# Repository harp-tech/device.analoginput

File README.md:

## Harp Analog Input

This device samples simultaneously up to 4 analog signals with 16 bits resolution, low noise and and analog input range of ±10 V for all channels.

### Key Features ###

* 4 ADC channels
* 16bit resolution with an input range of +-10V
* Simultaneous acquisition of all channels
* Threshold detection and event generation

### Connectivity ###

* 4 BNC connectors for analog input
* I/O connector for TTL signals

## Interface ##

The interface with the Harp board can be done through [Bonsai](https://bonsai-rx.org/)

## Licensing ##

Each subdirectory will contain a license or, possibly, a set of licenses if it involves both hardware and software.

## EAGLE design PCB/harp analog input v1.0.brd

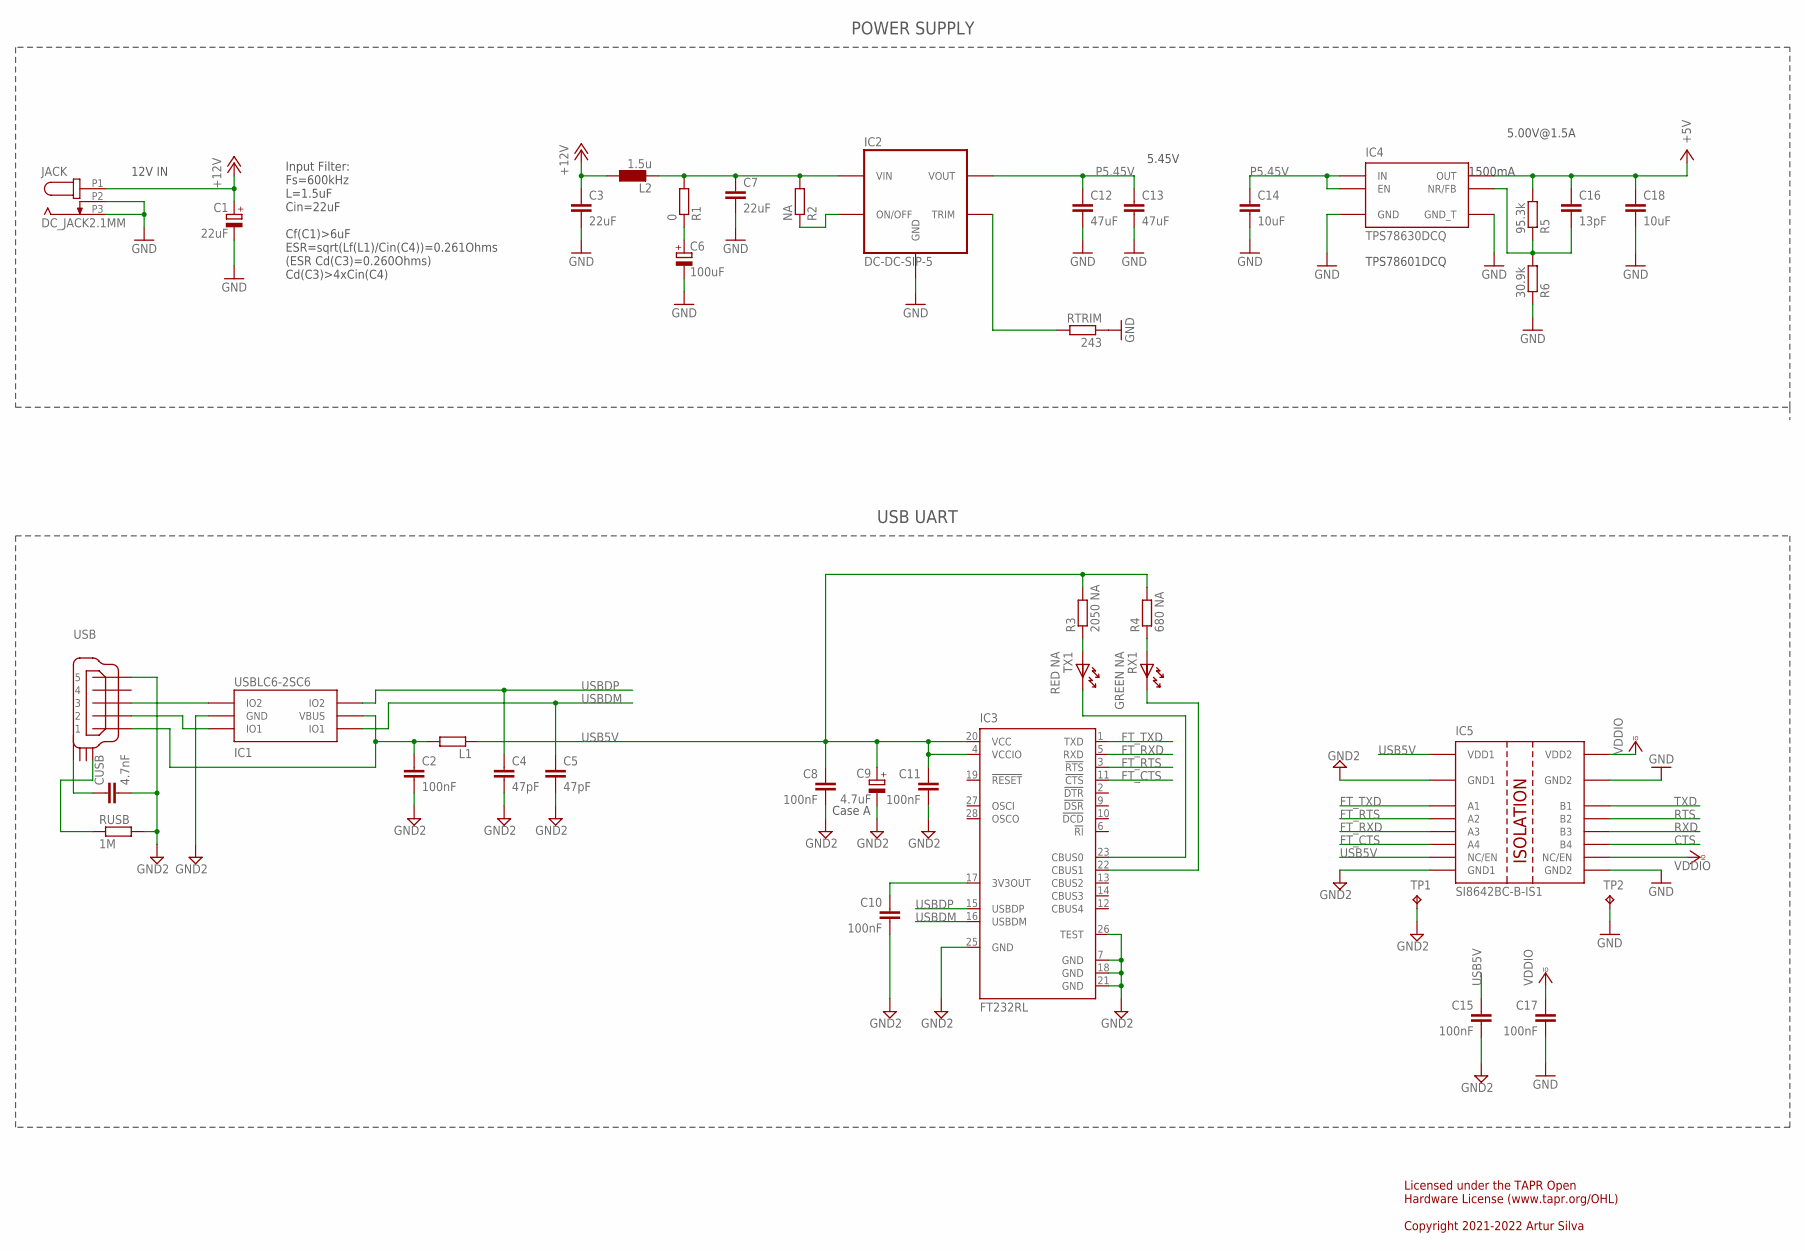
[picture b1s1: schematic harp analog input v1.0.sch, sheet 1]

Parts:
C1: 22uF; CAP_100UF_HAND
C2, C8, C10, C11, C15, C17: 100nF; C0402
C3, C7: 22uF; C1210
C4, C5: 47pF; C0402
C6: 100uF; PANASONIC_E
C9: 4.7uF; A/3216-18W
C12, C13: 47uF; C1210
C14, C18: 10uF; C0603
C16: 13pF; C0402
CUSB: 4.7nF; C0402
IC1: USBLC6-2SC6; SOT23-6L
IC2: DC-DC-SIP-5; SIP-5
IC3: FT232RL; SSOP28
IC4: TPS78630DCQ; SON-8
IC5: SI8642BC-B-IS1; NSOIC-16
JACK: DC_JACK2.1MM; DC_POWER_INPUT_2.1MM
L1: ???; R0805
L2: 1.5u; IND_LPS4012
R1: 0; R0402
R2: NA; R0402
R3: 2050 NA; R0402
R4: 680 NA; R0402
R5: 95.3k; R0402
R6: 30.9k; R0402
RTRIM: 243; R0402
RUSB: 1M; R0402
RX1: GREEN NA; LED_HAND
TP1, TP2: TPTP08SQ; TP08SQ
TX1: RED NA; LED_HAND
USB: USB_MINI_B; 240-0002-1

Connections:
3V3OUT: C10.1, IC3.17 (3V3OUT)
+5V: C16.1, C18.1, IC4.P3 (OUT), IC4.P4 (OUT), R5.2; also elsewhere on the board
+12V: C1.+, C3.1, JACK.P1 (1), L2.1
CTS: IC5.11 (B4); also elsewhere on the board
DCIN: C7.1, IC2.P2 (VIN), L2.2, R1.2, R2.2
FT_CTS: IC3.11 (!CTS), IC5.6 (A4)
FT_RTS: IC3.3 (!RTS), IC5.4 (A2)
FT_RXD: IC3.5 (RXD), IC5.5 (A3)
FT_TXD: IC3.1 (TXD), IC5.3 (A1)
GND: C1.-, C3.2, C6.-, C7.2, C12.2, C13.2, C14.2, C17.2, C18.2, IC2.P3 (GND), IC4.P6 (GND), IC4.P9 (GND_T), IC5.9 (GND2), IC5.15 (GND2), JACK.P2 (2), JACK.P3 (3), R6.1, RTRIM.1, TP2.TP; also elsewhere on the board
GND2: C2.2, C4.2, C5.2, C8.2, C9.-, C10.2, C11.2, C15.2, CUSB.2, IC1.P$2 (GND), IC3.7 (GND), IC3.18 (GND), IC3.21 (GND), IC3.25 (GND), IC3.26 (TEST), IC5.2 (GND1), IC5.8 (GND1), RUSB.2, TP1.TP, USB.P$5 (5)
unnamed: R4.1, RX1.A
unnamed: IC3.22 (CBUS1), RX1.K
unnamed: IC2.P5 (TRIM), RTRIM.2
unnamed: IC1.P$3 (IO2), USB.P$3 (3)
unnamed: CUSB.1, USB.SHIELD_4
unnamed: IC2.P1 (ON/OFF), R2.1
unnamed: C16.2, IC4.P5 (NR/FB), R5.1, R6.2
unnamed: C6.+, R1.1
unnamed: C2.1, IC1.P$5 (VBUS), L1.2, USB.P$1 (1)
unnamed: R3.1, TX1.A
unnamed: IC3.23 (CBUS0), TX1.K
unnamed: RUSB.1, USB.SHIELD_1
unnamed: IC1.P$1 (IO1), USB.P$2 (2)
P5.45V: C12.1, C13.1, C14.1, IC2.P4 (VOUT), IC4.P1 (IN), IC4.P2 (IN), IC4.P8 (EN)
RTS: IC5.13 (B2); also elsewhere on the board
RXD: IC5.12 (B3); also elsewhere on the board
TXD: IC5.14 (B1); also elsewhere on the board
USB5V: C8.1, C9.+, C11.1, C15.1, IC3.4 (VCCIO), IC3.20 (VCC), IC5.1 (VDD1), IC5.7 (NC/EN), L1.1, R3.2, R4.2
USBDM: C5.1, IC1.P$6 (IO1), IC3.16 (USBDM)
USBDP: C4.1, IC1.P$4 (IO2), IC3.15 (USBDP)
VCCIO: C17.1, IC5.10 (NC/EN), IC5.16 (VDD2); also elsewhere on the board

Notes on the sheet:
12V IN
5.45V
1500mA
TPS78601DCQ
5.00V@1.5A
Input Filter: Fs=600kHz L=1.5uF Cin=22uF Cf(C1)>6uF ESR=sqrt(Lf(L1)/Cin(C4))=0.261Ohms (ESR Cd(C3)=0.260Ohms) Cd(C3)>4xCin(C4)
Case A
USB UART
Licensed under the TAPR Open Hardware License (www.tapr.org/OHL) Copyright 2021-2022 Artur Silva
POWER SUPPLY

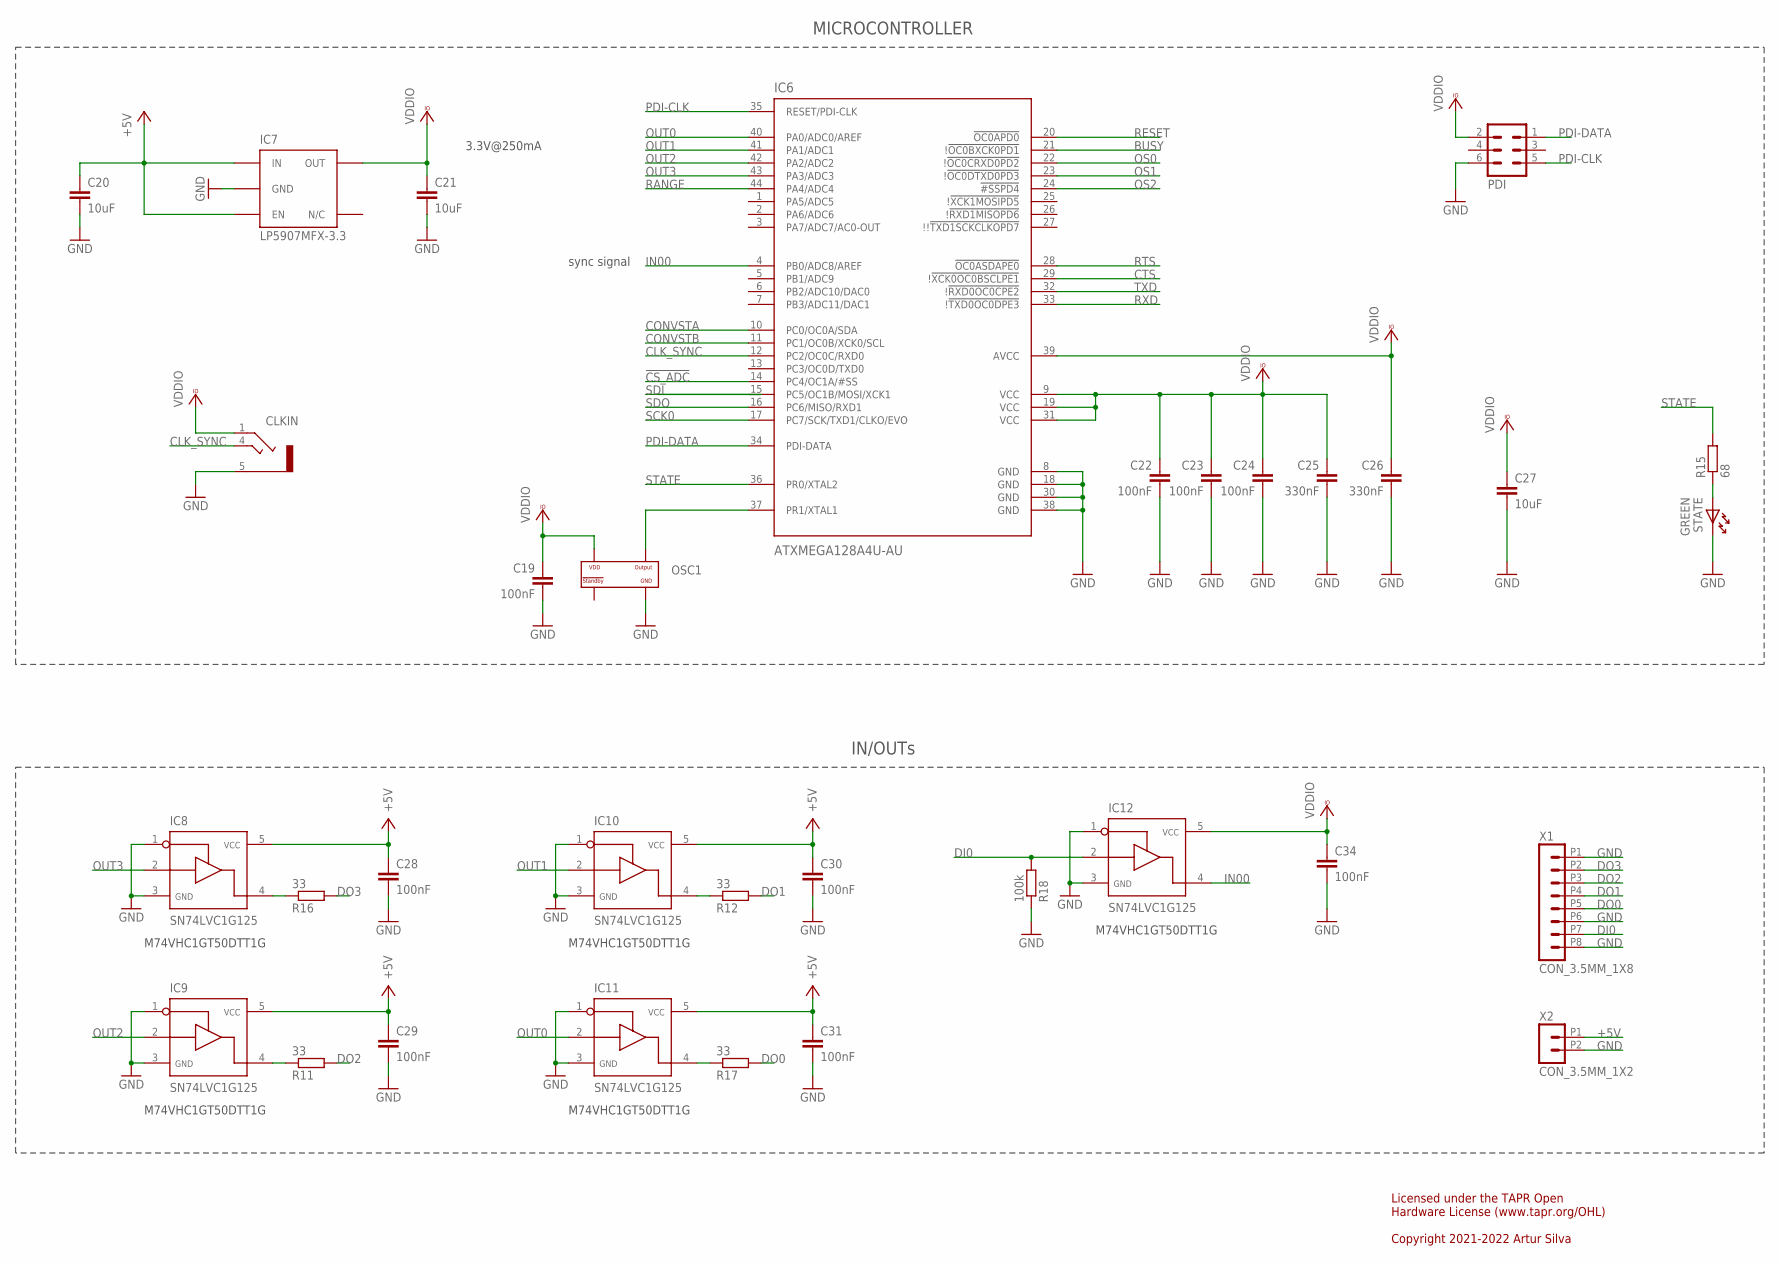
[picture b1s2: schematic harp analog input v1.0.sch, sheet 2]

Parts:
C19, C22, C23, C24, C28, C29, C30, C31, C34: 100nF; C0402
C20, C21, C27: 10uF; C0603
C25, C26: 330nF; C0402
CLKIN: STEREO_JACK; 35RASMT2BHNTRX
IC6: ATXMEGA128A4U-AU; QFP80P1200X1200X120-44N
IC7: LP5907MFX-3.3; TSOT23-5
IC8, IC9, IC10, IC11, IC12: SN74LVC1G125; SOT23-5
OSC1: OSCILLATOR; OSCILLATOR_3.2X2.5
PDI: MA03-2
R11, R12, R16, R17: 33; R0402
R15: 68; R0402
R18: 100k; R0402
STATE: GREEN; LED_HAND
X1: CON_3.5MM_1X8
X2: CON_3.5MM_1X2

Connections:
!CS_ADC: IC6.14 (PC4/OC1A/#SS); also elsewhere on the board
+5V: C20.1, C28.1, C29.1, C30.1, C31.1, IC7.1 (IN), IC7.3 (EN), IC8.5, IC9.5, IC10.5, IC11.5, X2.P1 (1); also elsewhere on the board
BUSY: IC6.21 (!!OC0BXCK0PD1); also elsewhere on the board
CLK_SYNC: CLKIN.4, IC6.12 (PC2/OC0C/RXD0)
CONVSTA: IC6.10 (PC0/OC0A/SDA); also elsewhere on the board
CONVSTB: IC6.11 (PC1/OC0B/XCK0/SCL); also elsewhere on the board
CTS: IC6.29 (!!XCK0OC0BSCLPE1); also elsewhere on the board
DI0: IC12.2, R18.2, X1.P7 (7)
DO0: R17.2, X1.P5 (5)
DO1: R12.2, X1.P4 (4)
DO2: R11.2, X1.P3 (3)
DO3: R16.2, X1.P2 (2)
GND: C19.2, C20.2, C21.2, C22.2, C23.2, C24.2, C25.2, C26.2, C27.2, C28.2, C29.2, C30.2, C31.2, C34.2, CLKIN.5, IC6.8 (GND), IC6.18 (GND), IC6.30 (GND), IC6.38 (GND), IC7.2 (GND), IC8.1, IC8.3, IC9.1, IC9.3, IC10.1, IC10.3, IC11.1, IC11.3, IC12.1, IC12.3, OSC1.P$2 (GND), PDI.6, R18.1, STATE.K, X1.P1 (1), X1.P6 (6), X1.P8 (8), X2.P2 (2); also elsewhere on the board
IN00: IC6.4 (PB0/ADC8/AREF), IC12.4
unnamed: IC9.4, R11.1
unnamed: IC10.4, R12.1
unnamed: IC11.4, R17.1
unnamed: IC8.4, R16.1
unnamed: R15.1, STATE.A
OS0: IC6.22 (!!OC0CRXD0PD2); also elsewhere on the board
OS1: IC6.23 (!!OC0DTXD0PD3); also elsewhere on the board
OS2: IC6.24 (!#SSPD4); also elsewhere on the board
OSC1: IC6.37 (PR1/XTAL1), OSC1.P$3 (OUTPUT)
OUT0: IC6.40 (PA0/ADC0/AREF), IC11.2
OUT1: IC6.41 (PA1/ADC1), IC10.2
OUT2: IC6.42 (PA2/ADC2), IC9.2
OUT3: IC6.43 (PA3/ADC3), IC8.2
PDI-CLK: IC6.35 (RESET/PDI-CLK), PDI.5
PDI-DATA: IC6.34 (PDI-DATA), PDI.1
RANGE: IC6.44 (PA4/ADC4); also elsewhere on the board
RESET: IC6.20 (!OC0APD0); also elsewhere on the board
RTS: IC6.28 (!OC0ASDAPE0); also elsewhere on the board
RXD: IC6.33 (!!TXD0OC0DPE3); also elsewhere on the board
SCK0: IC6.17 (PC7/SCK/TXD1/CLKO/EVO); also elsewhere on the board
SDI: IC6.15 (PC5/OC1B/MOSI/XCK1)
SDO: IC6.16 (PC6/MISO/RXD1); also elsewhere on the board
STATE: IC6.36 (PR0/XTAL2), R15.2
TXD: IC6.32 (!!RXD0OC0CPE2); also elsewhere on the board
VCCIO: C19.1, C21.1, C22.1, C23.1, C24.1, C25.1, C26.1, C27.1, C34.1, CLKIN.1, IC6.9 (VCC), IC6.19 (VCC), IC6.31 (VCC), IC6.39 (AVCC), IC7.5 (OUT), IC12.5, OSC1.P$4 (VDD), PDI.2; also elsewhere on the board

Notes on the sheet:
3.3V@250mA
sync signal
Licensed under the TAPR Open Hardware License (www.tapr.org/OHL) Copyright 2021-2022 Artur Silva
M74VHC1GT50DTT1G
MICROCONTROLLER
IN/OUTs

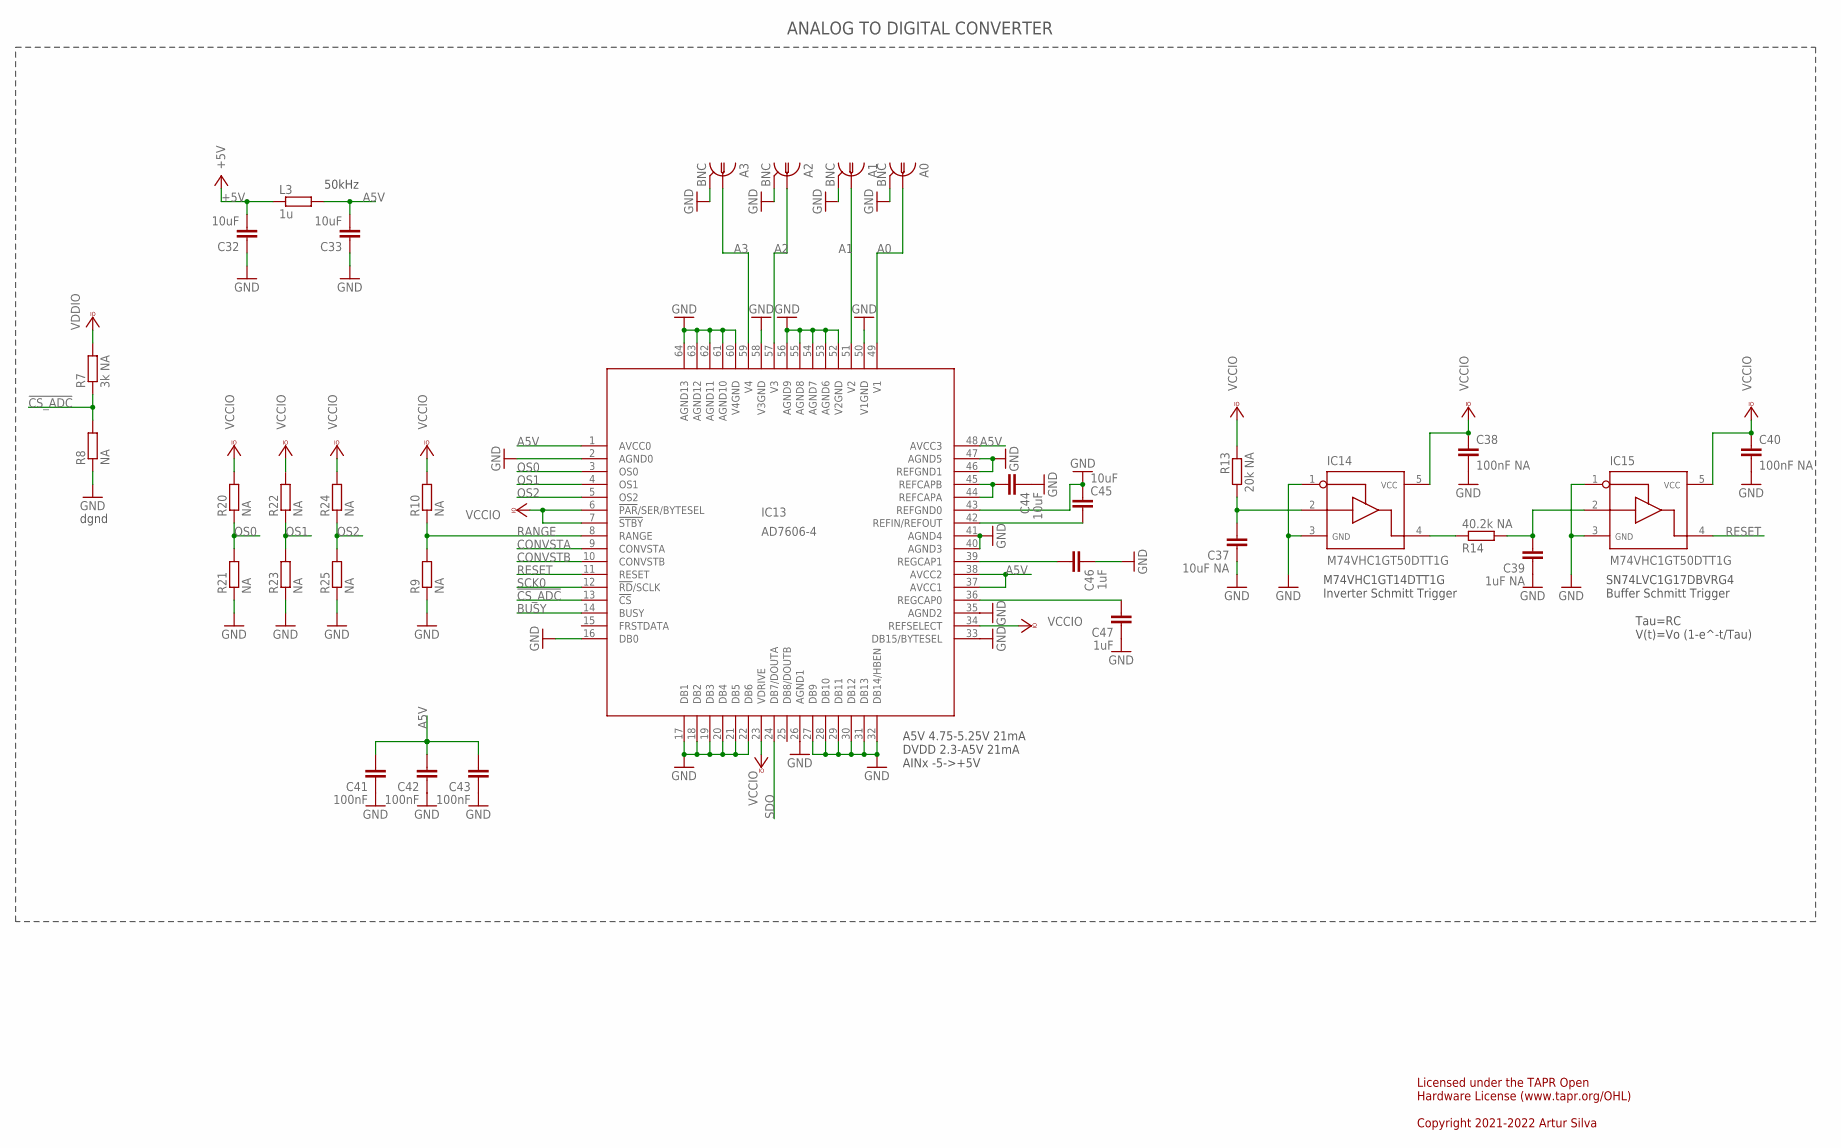
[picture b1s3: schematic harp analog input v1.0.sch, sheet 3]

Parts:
A0, A1, A2, A3: BNC; BNC_RA
C32, C33, C44, C45: 10uF; C0603
C37: 10uF NA; C0603
C38, C40: 100nF NA; C0402
C39: 1uF NA; C0402
C41, C42, C43: 100nF; C0402
C46, C47: 1uF; C0402
IC13: AD7606-4; LQFP-64
IC14, IC15: M74VHC1GT50DTT1G; SOT23-5
L3: 1u; R0402
R7: 3k NA; R0402
R8, R9, R10, R20, R21, R22, R23, R24, R25: NA; R0402
R13: 20k NA; R0402
R14: 40.2k NA; R0402

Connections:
!CS_ADC: IC13.13 (!CS), R7.1, R8.2; also elsewhere on the board
+5V: C32.2, L3.1; also elsewhere on the board
A0: A0.1, IC13.49 (V1)
A1: A1.1, IC13.51 (V2)
A2: A2.1, IC13.57 (V3)
A3: A3.1, IC13.59 (V4)
A5V: C33.2, C41.2, C42.2, C43.2, IC13.1 (AVCC0), IC13.37 (AVCC1), IC13.38 (AVCC2), IC13.48 (AVCC3), L3.2
BUSY: IC13.14 (BUSY); also elsewhere on the board
CONVSTA: IC13.9 (CONVSTA); also elsewhere on the board
CONVSTB: IC13.10 (CONVSTB); also elsewhere on the board
GND: A0.2, A1.2, A2.2, A3.2, C32.1, C33.1, C37.1, C38.2, C39.1, C40.2, C41.1, C42.1, C43.1, C44.1, C45.1, C46.1, C47.1, IC13.2 (AGND0), IC13.16 (DB0), IC13.17 (DB1), IC13.18 (DB2), IC13.19 (DB3), IC13.20 (DB4), IC13.21 (DB5), IC13.22 (DB6), IC13.26 (AGND1), IC13.27 (DB9), IC13.28 (DB10), IC13.29 (DB11), IC13.30 (DB12), IC13.31 (DB13), IC13.32 (DB14/HBEN), IC13.33 (DB15/BYTESEL), IC13.35 (AGND2), IC13.40 (AGND3), IC13.41 (AGND4), IC13.43 (REFGND0), IC13.46 (REFGND1), IC13.47 (AGND5), IC13.50 (V1GND), IC13.52 (V2GND), IC13.53 (AGND6), IC13.54 (AGND7), IC13.55 (AGND8), IC13.56 (AGND9), IC13.58 (V3GND), IC13.60 (V4GND), IC13.61 (AGND10), IC13.62 (AGND11), IC13.63 (AGND12), IC13.64 (AGND13), IC14.1, IC14.3, IC15.1, IC15.3, R8.1, R9.1, R21.1, R23.1, R25.1; also elsewhere on the board
unnamed: C47.2, IC13.36 (REGCAP0)
unnamed: C46.2, IC13.39 (REGCAP1)
unnamed: C45.2, IC13.42 (REFIN/REFOUT)
unnamed: C44.2, IC13.44 (REFCAPA), IC13.45 (REFCAPB)
unnamed: C37.2, IC14.2, R13.2
unnamed: IC14.4, R14.1
unnamed: C39.2, IC15.2, R14.2
OS0: IC13.3 (OS0), R20.1, R21.2; also elsewhere on the board
OS1: IC13.4 (OS1), R22.1, R23.2; also elsewhere on the board
OS2: IC13.5 (OS2), R24.1, R25.2; also elsewhere on the board
RANGE: IC13.8 (RANGE), R9.2, R10.1; also elsewhere on the board
RESET: IC13.11 (RESET), IC15.4; also elsewhere on the board
SCK0: IC13.12 (!RD!/SCLK); also elsewhere on the board
SDO: IC13.24 (DB7/DOUTA); also elsewhere on the board
VCCIO: C38.1, C40.1, IC13.6 (!PAR!/SER/BYTESEL), IC13.7 (!STBY), IC13.23 (VDRIVE), IC13.34 (REFSELECT), IC14.5, IC15.5, R7.2, R10.2, R13.1, R20.2, R22.2, R24.2; also elsewhere on the board

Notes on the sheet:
A5V 4.75-5.25V 21mA DVDD 2.3-A5V 21mA AINx -5->+5V
50kHz
M74VHC1GT14DTT1G Inverter Schmitt Trigger
SN74LVC1G17DBVRG4 Buffer Schmitt Trigger
Tau=RC V(t)=Vo (1-e^-t/Tau)
dgnd
Licensed under the TAPR Open Hardware License (www.tapr.org/OHL) Copyright 2021-2022 Artur Silva
ANALOG TO DIGITAL CONVERTER

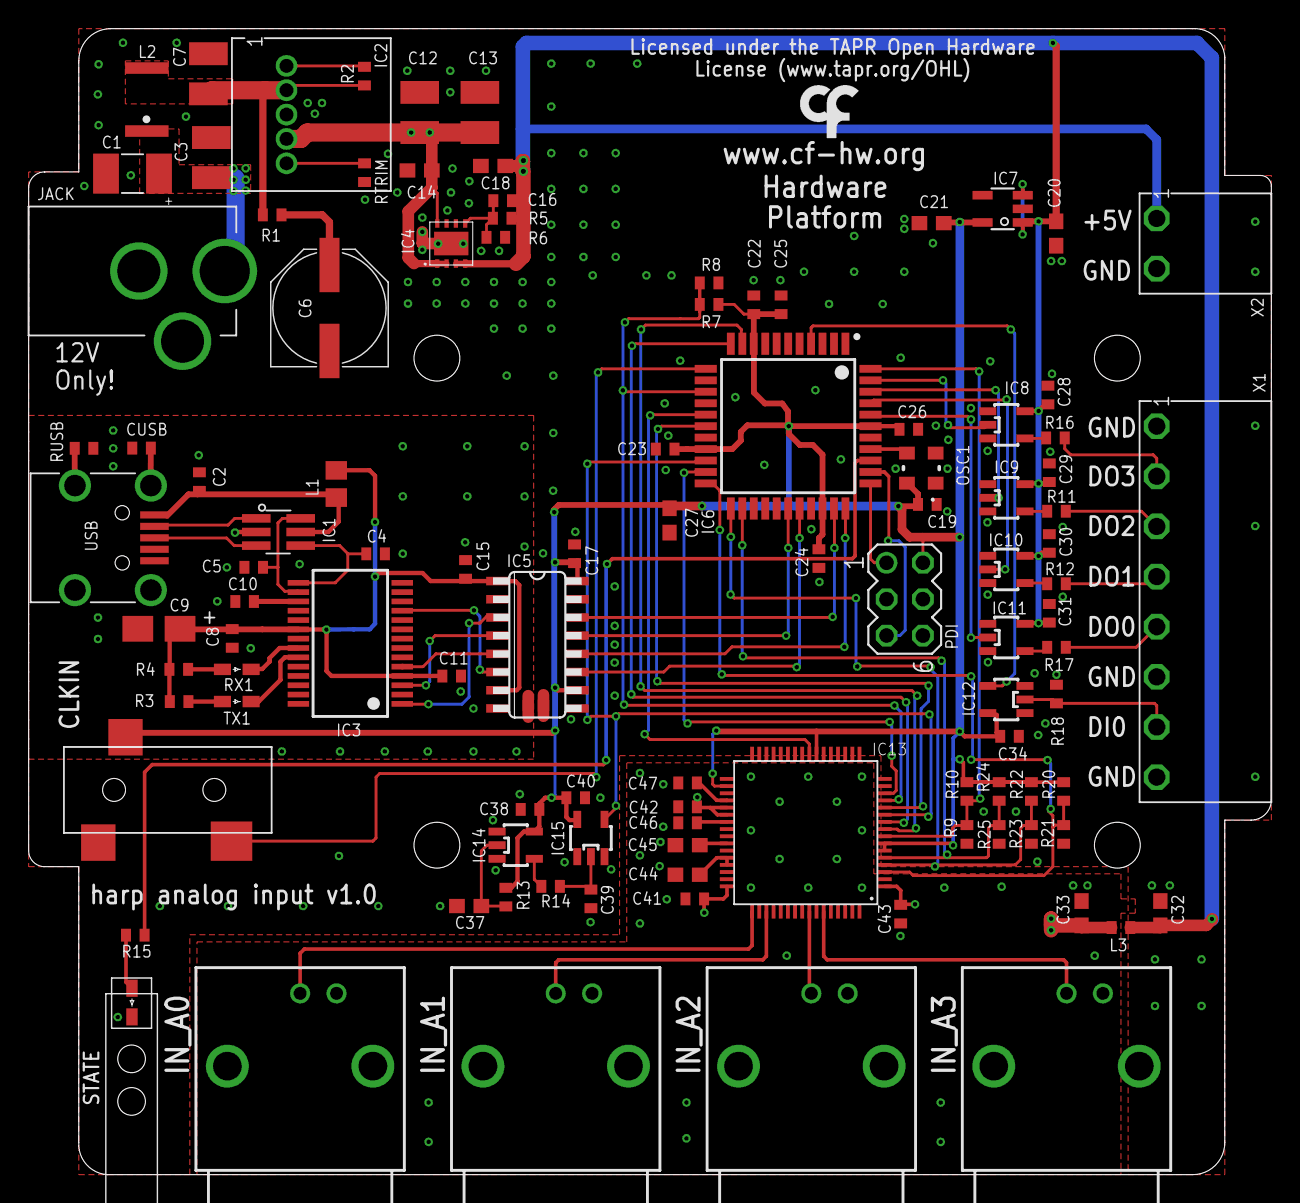
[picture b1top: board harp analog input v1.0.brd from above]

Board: 2 copper layers, 86.8 x 80.0 mm, 109 parts (1 on the bottom side), 75 nets.

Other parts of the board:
U$2: LOGO_5
U$3: LED_PIPE_7513D2-L
U$4: LOGO_7

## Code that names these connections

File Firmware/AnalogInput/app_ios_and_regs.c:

#include <avr/io.h>
#include "hwbp_core_types.h"
#include "app_ios_and_regs.h"

/************************************************************************/
/* Configure and initialize IOs                                         */
/************************************************************************/
void init_ios(void)
{	/* Configure input pins */
	io_pin2in(&PORTB, 0, PULL_IO_UP, SENSE_IO_EDGES_BOTH);               // DI0
	io_pin2in(&PORTC, 6, PULL_IO_UP, SENSE_IO_EDGES_BOTH);               // MISO
	io_pin2in(&PORTD, 1, PULL_IO_UP, SENSE_IO_EDGE_FALLING);             // BUSY

	/* Configure input interrupts */
	io_set_int(&PORTB, INT_LEVEL_LOW, 0, (1<<0), false);                 // DI0
	io_set_int(&PORTD, INT_LEVEL_LOW, 0, (1<<1), false);                 // BUSY

	/* Configure output pins */
	io_pin2out(&PORTA, 0, OUT_IO_DIGITAL, IN_EN_IO_EN);                  // DO0
	io_pin2out(&PORTA, 1, OUT_IO_DIGITAL, IN_EN_IO_EN);                  // DO1
	io_pin2out(&PORTA, 2, OUT_IO_DIGITAL, IN_EN_IO_EN);                  // DO2
	io_pin2out(&PORTA, 3, OUT_IO_DIGITAL, IN_EN_IO_EN);                  // DO3
	io_pin2out(&PORTC, 4, OUT_IO_DIGITAL, IN_EN_IO_EN);                  // CS_ADC
	io_pin2out(&PORTC, 0, OUT_IO_DIGITAL, IN_EN_IO_EN);                  // CONVSTA
	io_pin2out(&PORTC, 1, OUT_IO_DIGITAL, IN_EN_IO_EN);                  // CONVSTB
	io_pin2out(&PORTC, 5, OUT_IO_DIGITAL, IN_EN_IO_DIS);                 // MOSI
	io_pin2out(&PORTC, 7, OUT_IO_DIGITAL, IN_EN_IO_DIS);                 // SCK
	io_pin2out(&PORTD, 0, OUT_IO_DIGITAL, IN_EN_IO_EN);                  // RESET
	io_pin2out(&PORTD, 2, OUT_IO_DIGITAL, IN_EN_IO_EN);                  // OS0
	io_pin2out(&PORTD, 3, OUT_IO_DIGITAL, IN_EN_IO_DIS);                 // OS1
	io_pin2out(&PORTD, 4, OUT_IO_DIGITAL, IN_EN_IO_DIS);                 // OS2
	io_pin2out(&PORTA, 4, OUT_IO_DIGITAL, IN_EN_IO_EN);                  // RANGE

	/* Initialize output pins */
	clr_DO0;
	clr_DO1;
	clr_DO2;
	clr_DO3;
	set_CS_ADC;
	clr_CONVSTA;
	clr_CONVSTB;
	clr_MOSI;
	clr_SCK;
	clr_RESET;
	clr_OS0;
	set_OS1;
	set_OS2;
	clr_RANGE;
}

/************************************************************************/
/* Registers' stuff                                                     */
/************************************************************************/
AppRegs app_regs;

uint8_t app_regs_type[] = {
	TYPE_U8,
	TYPE_I16,
	TYPE_U8,
	TYPE_U8,
	TYPE_U8,
	TYPE_U8,
	TYPE_U8,
	TYPE_U8,
	TYPE_U8,
	TYPE_U8,
	TYPE_U8,
	TYPE_U8,
	TYPE_U8,
	TYPE_U8,
	TYPE_U8,
	TYPE_U8,
	TYPE_U8,
	TYPE_U8,
	TYPE_U8,
	TYPE_U8,
	TYPE_U8,
	TYPE_U8,
	TYPE_U8,
	TYPE_U8,
	TYPE_U8,
	TYPE_U8,
	TYPE_U8,
	TYPE_U8,
	TYPE_U8,
	TYPE_U8,
	TYPE_U8,
	TYPE_U8,
	TYPE_U8,
	TYPE_U8,
	TYPE_I16,
	TYPE_I16,
	TYPE_I16,
	TYPE_I16,
	TYPE_U8,
	TYPE_U8,
	TYPE_U8,
	TYPE_U8,
	TYPE_U16,
	TYPE_U16,
	TYPE_U16,
	TYPE_U16,
	TYPE_U8,
	TYPE_U8,
	TYPE_U8,
	TYPE_U8,
	TYPE_U16,
	TYPE_U16,
	TYPE_U16,
	TYPE_U16,
	TYPE_U8,
	TYPE_U8,
	TYPE_U8,
	TYPE_U8,
	TYPE_U8
};

uint16_t app_regs_n_elements[] = {
	1,
	4,
	1,
	1,
	1,
	1,
	1,
	1,
	1,
	1,
	1,
	1,
	1,
	1,
	1,
	1,
	1,
	1,
	1,
	1,
	1,
	1,
	1,
	1,
	1,
	1,
	1,
	1,
	1,
	1,
	1,
	1,
	1,
	1,
	1,
	1,
	1,
	1,
	1,
	1,
	1,
	1,
	1,
	1,
	1,
	1,
	1,
	1,
	1,
	1,
	1,
	1,
	1,
	1,
	1,
	1,
	1,
	1,
	1
};

uint8_t *app_regs_pointer[] = {
	(uint8_t*)(&app_regs.REG_START),
	(uint8_t*)(app_regs.REG_ANALOG_INPUTS),
	(uint8_t*)(&app_regs.REG_DI0),
	(uint8_t*)(&app_regs.REG_RESERVED0),
	(uint8_t*)(&app_regs.REG_RESERVED00),
	(uint8_t*)(&app_regs.REG_RANGE_AND_INPUT_FILTER),
	(uint8_t*)(&app_regs.REG_SAMPLE_FREQUENCY),
	(uint8_t*)(&app_regs.REG_DI0_CONF),
	(uint8_t*)(&app_regs.REG_DO0_CONF),
	(uint8_t*)(&app_regs.REG_DO0_PULSE),
	(uint8_t*)(&app_regs.REG_DO_SET),
	(uint8_t*)(&app_regs.REG_DO_CLEAR),
	(uint8_t*)(&app_regs.REG_DO_TOGGLE),
	(uint8_t*)(&app_regs.REG_DO_WRITE),
	(uint8_t*)(&app_regs.REG_RESERVED1),
	(uint8_t*)(&app_regs.REG_RESERVED2),
	(uint8_t*)(&app_regs.REG_TRIGGER_DESTINY),
	(uint8_t*)(&app_regs.REG_RESERVED3),
	(uint8_t*)(&app_regs.REG_RESERVED4),
	(uint8_t*)(&app_regs.REG_RESERVED5),
	(uint8_t*)(&app_regs.REG_RESERVED6),
	(uint8_t*)(&app_regs.REG_RESERVED7),
	(uint8_t*)(&app_regs.REG_RESERVED8),
	(uint8_t*)(&app_regs.REG_RESERVED9),
	(uint8_t*)(&app_regs.REG_RESERVED10),
	(uint8_t*)(&app_regs.REG_RESERVED11),
	(uint8_t*)(&app_regs.REG_DO0_CH),
	(uint8_t*)(&app_regs.REG_DO1_CH),
	(uint8_t*)(&app_regs.REG_DO2_CH),
	(uint8_t*)(&app_regs.REG_DO3_CH),
	(uint8_t*)(&app_regs.REG_RESERVED12),
	(uint8_t*)(&app_regs.REG_RESERVED13),
	(uint8_t*)(&app_regs.REG_RESERVED14),
	(uint8_t*)(&app_regs.REG_RESERVED15),
	(uint8_t*)(&app_regs.REG_DO0_TH_VALUE),
	(uint8_t*)(&app_regs.REG_DO1_TH_VALUE),
	(uint8_t*)(&app_regs.REG_DO2_TH_VALUE),
	(uint8_t*)(&app_regs.REG_DO3_TH_VALUE),
	(uint8_t*)(&app_regs.REG_RESERVED17),
	(uint8_t*)(&app_regs.REG_RESERVED18),
	(uint8_t*)(&app_regs.REG_RESERVED19),
	(uint8_t*)(&app_regs.REG_RESERVED20),
	(uint8_t*)(&app_regs.REG_DO0_TH_UP_SAMPLES),
	(uint8_t*)(&app_regs.REG_DO1_TH_UP_SAMPLES),
	(uint8_t*)(&app_regs.REG_DO2_TH_UP_SAMPLES),
	(uint8_t*)(&app_regs.REG_DO3_TH_UP_SAMPLES),
	(uint8_t*)(&app_regs.REG_RESERVED21),
	(uint8_t*)(&app_regs.REG_RESERVED22),
	(uint8_t*)(&app_regs.REG_RESERVED23),
	(uint8_t*)(&app_regs.REG_RESERVED24),
	(uint8_t*)(&app_regs.REG_DO0_TH_DOWN_SAMPLES),
	(uint8_t*)(&app_regs.REG_DO1_TH_DOWN_SAMPLES),
	(uint8_t*)(&app_regs.REG_DO2_TH_DOWN_SAMPLES),
	(uint8_t*)(&app_regs.REG_DO3_TH_DOWN_SAMPLES),
	(uint8_t*)(&app_regs.REG_RESERVED25),
	(uint8_t*)(&app_regs.REG_RESERVED26),
	(uint8_t*)(&app_regs.REG_RESERVED27),
	(uint8_t*)(&app_regs.REG_RESERVED28),
	(uint8_t*)(&app_regs.REG_RESERVED29)
};

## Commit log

2021-11-24 Create .gitignore
    Added .gitignore
2021-11-24 Create README.md
    Added README.md
2021-12-15 Create PCB folder and added license files
2021-12-15 Added PCB design files
2021-12-15 Update description
2021-12-20 Re-organized DO alignment from left (DO0) to right (DO3)
2021-12-20 Correct minor DRC and net labelling from merge
2022-04-12 Added first firmware files.
2022-04-12 Implemented all firmware features except the digital outputs.
2022-11-18 Add CONVST pin/swap CS_ADC
    To allow for future higher speed acquisitions
2022-11-18 Dual CONVST support added
2023-04-17 Remove legacy examples
2023-04-17 Add first draft of device schema
2023-04-17 Add interface generators
2023-04-17 Add generated Device classes
2023-04-19 Minor naming change
2023-04-19 Improve schema consistency with device.loadcells
2023-04-19 Update interface to reflect latest schema specs
2023-04-20 Favor "PulseWidth" over "PulseDuration"
2023-04-24 Refactor schema for consistency
2023-05-03 Add PCB image
2023-05-15 Resize PCB image
2023-05-20 Renamed pin CONVST to CONVSTA
2023-05-20 Minor details
2023-05-20 Made the library path relative
2023-05-20 Fix Digital Output pins
2023-06-02 Update Device classes to new schema
2023-06-02 Improve readability of schema
2023-06-02 Update `Device` classes to new schema
2023-06-07 Improve schema for consistency with Device.LoadCells
2023-06-07 Increment preview
2023-06-28 Fix indentation
2023-06-28 Update ADC filter mask values
2023-07-03 Updated limit for the Digital Output 0 pulse.
2023-07-03 Increased fw version to 1.2.
2023-07-03 Get initial state of Digital Input 0.
2023-07-03 Changed RESET line to push-pull.
2023-07-03 Implemented ability to read the Digital Input 0 state.
2023-07-03 Removed catch sample on the falling edge.
2023-07-03 Changed threshold detection routine to be more efficient.
2023-07-03 Added control of the Digital Output lines.
2023-07-04 Increased harp core to 1.12.
2023-07-04 Added a bonsai workflow used for tests and development.
2023-07-04 Removed catch sample on the falling edge from schema.
2023-07-05 Changed threshold registers to public.
2023-07-05 Updated firmware version.
2023-07-06 Renamed Bonsai test script.
2023-07-31 Update interface to use new generators
2023-08-03 Add interface license and package stable version
2023-08-03 Add missing package metadata
2023-08-03 Always generate documentation file
2023-08-03 Update license and project format for consistency
2023-08-10 Updated dates.
2023-08-10 Replaced harp core 1.12 with 1.13.
2023-08-19 Move folder and rename licenses
2023-08-19 Add mechanical folder and license
2023-08-19 Add .gitignore to Hardware
2024-11-09 Fix schema source
2024-11-09 Update generators and regenerate interface
2024-11-09 Update package metadata to embed device metadata
2024-11-10 Favor harp-tech as source of device schema
2025-06-12 Create basic CI/CD for interface package
2025-10-23 Updated to atxmega core 1.15

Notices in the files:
PCB/harp analog input v1.0.brd:
Copyright 2021 Hardware Platform
